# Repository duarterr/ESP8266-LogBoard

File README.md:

# ESP8266 LogBoard

A development platform for the ESP8266 with data logger capabilities. Fully compatible with the Arduino IDE.

Author: Renan R. Duarte - <duarte.renan@hotmail.com>

## Features
 - **ESP8266 (ESP12E) microcontroller:** The board is based on the ESP12E module, featuring the ESP8266 microcontroller. The module is configured in DIO SPI mode, so two extras GPIO pins can be used by the application (13 GPIOs in total).
 - **MicroSD card:** Data can be easily stored in a standard microSD card.
 - **Temperature sensor:** The Maxim DS1722 SPI temperature sensor can be used to measure the temperature.
 - **Real-time clock:** A Maxim DS1391 battery-backed SPI real-time clock provides timing capabilities without needing the internet.
 - **Onboard battery charger:** The board can be powered directly from the USB port or by a lithium battery. The onboard battery charger can be configured to fully charge the battery (4.2V) for cyclic use or float charge with a lower voltage (4.1V) to extend battery life in applications where the USB power is always connected.
 - **Switched-mode power supply:** A Maxim MAX8625 buck-boost controller IC provides a high efficiency continuous 3.3V bus to the system.
 - **Onboard programmer:** The device can be programmed directly by the USB port using the onboard USB-Serial bridge (FTDI FT232RQ). This device also enables serial communications between the microcontroller and a PC.

## Repository Contents

* **/Hardware** - PCB related files (EAGLE v9.5.5 and Sketchup 2018).
* **/Firmware** - Arduino example sketches to make use of it. 
* **/Extras** - Images and other stuff. 

## License Information

All contents of this repository are released under [Creative Commons Share-alike 4.0](http://creativecommons.org/licenses/by-sa/4.0/).

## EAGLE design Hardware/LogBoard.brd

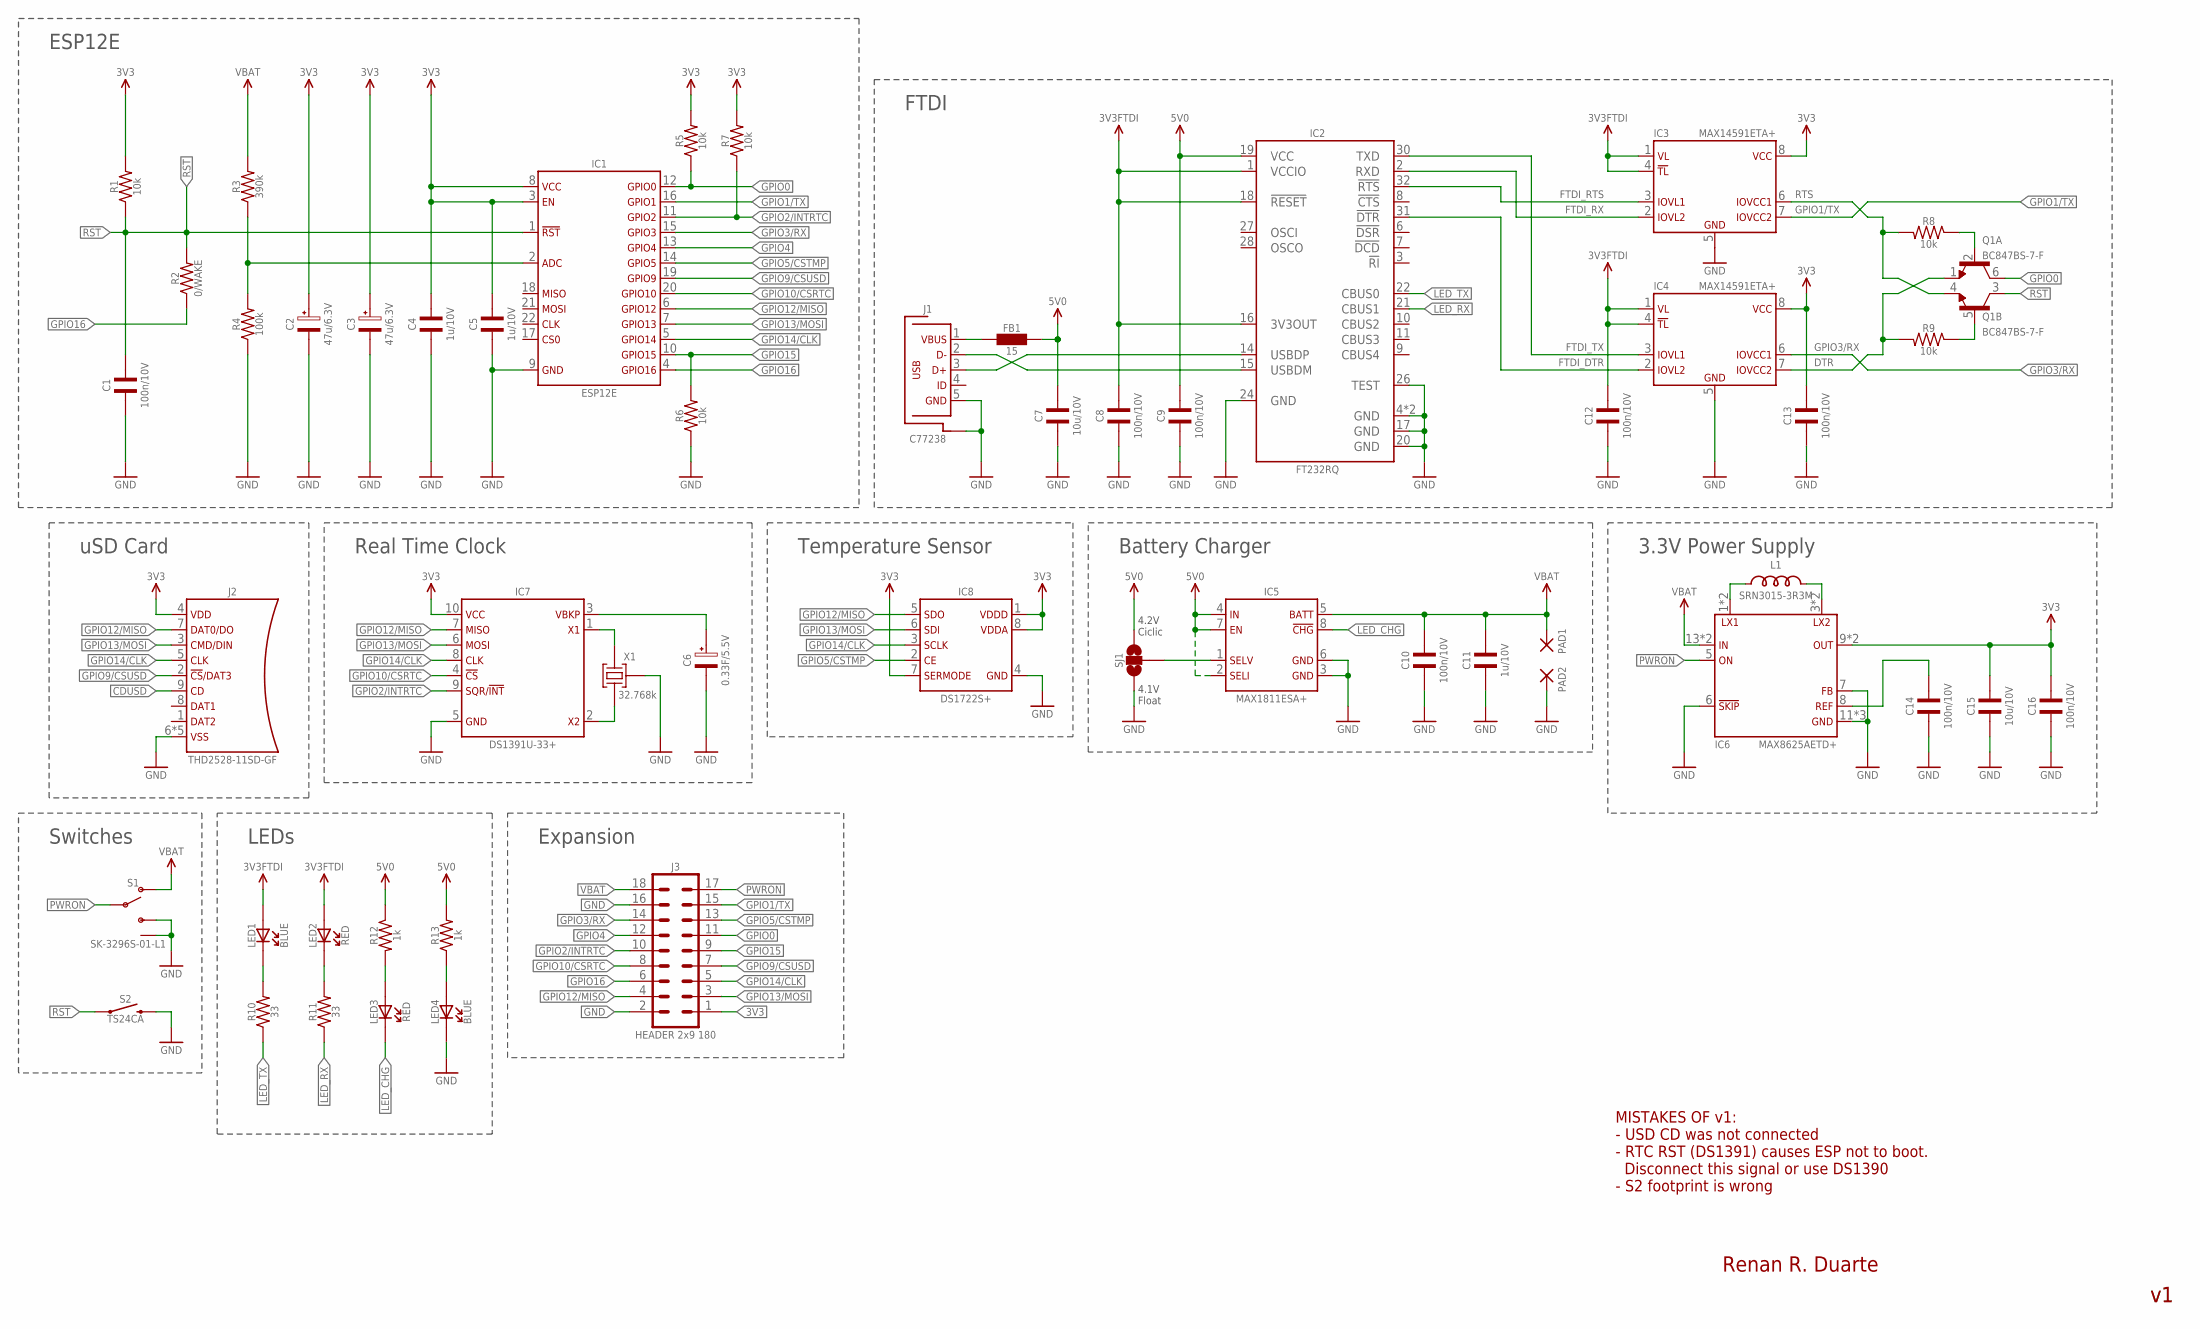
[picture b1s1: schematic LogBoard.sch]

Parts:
C1, C8, C9, C10, C12, C13, C14, C16: 100n/10V; C-SMD-0603
C2, C3: 47u/6.3V; C-SMD-CT3528
C4, C5, C11: 1u/10V; C-SMD-0603
C6: 0.33F/5.5V; C-PTH-5X11.5
C7, C15: 10u/10V; C-SMD-0603
FB1: 15; R-SMD-0603
IC1: ESP12E; IC-ESP8266-12E
IC2: FT232RQ; IC-QFN32
IC3, IC4: MAX14591ETA+; IC-TDFN8
IC5: MAX1811ESA+; IC-SO8
IC6: MAX8625AETD+; IC-TDFN14
IC7: DS1391U-33+; IC-USOP10
IC8: DS1722S+; IC-SO8
J1: C77238; CN-MICRO-USB
J2: THD2528-11SD-GF; CN-MICROSD
J3: HEADER 2x9 180; PH-9X2-180
L1: SRN3015-3R3M; L-SMD-3X3
LED1, LED4: BLUE; LED-SMD-0603
LED2, LED3: RED; LED-SMD-0603
PAD1, PAD2: SMD2; SMD1,27-2,54
Q1: BC847BS-7-F; IC-SOT363
R1, R5, R6, R7, R8, R9: 10k; R-SMD-0603
R2: 0/WAKE; R-SMD-0603
R3: 390k; R-SMD-0603
R4: 100k; R-SMD-0603
R10, R11: 33; R-SMD-0603
R12, R13: 1k; R-SMD-0603
S1: SK-3296S-01-L1; SWITCH_SPST_SMD_A
S2: TS24CA; TACTILE_SWITCH_SMD_RIGHT_ANGLE
SJ1: SJ-3
X1: 32.768k; CRYSTAL-SMD-7X1.5

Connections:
3V3: C2.+, C3.+, C4.P$1 (1), C5.P$1 (1), C13.P$2 (2), C15.P$1 (1), C16.P$1 (1), IC1.3 (EN), IC1.8 (VCC), IC3.8 (VCC), IC4.8 (VCC), IC6.9 (OUT), IC6.10 (OUT), IC7.10 (VCC), IC8.1 (VDDD), IC8.7 (SERMODE), IC8.8 (VDDA), J2.4 (VDD), J3.1, R1.P$2 (2), R5.P$2 (2), R7.P$2 (2)
3V3FTDI: C8.P$2 (2), C12.P$2 (2), IC2.1 (VCCIO), IC2.16 (3V3OUT), IC2.18 (!RESET), IC3.1 (VL), IC3.4 (!TL), IC4.1 (VL), IC4.4 (!TL), LED1.A, LED2.A
5V0: C7.P$2 (2), C9.P$2 (2), FB1.P$2 (2), IC2.19 (VCC), IC5.2 (SELI), IC5.4 (IN), IC5.7 (EN), R12.P$1 (1), R13.P$2 (2), SJ1.1
CDUSD: J2.9 (CD)
DTR: IC4.7 (IOVCC2), Q1.1 (E), R9.P$2 (2)
FTDI_DTR: IC2.31 (!DTR), IC4.2 (IOVL2)
FTDI_RTS: IC2.32 (!RTS), IC3.3 (IOVL1)
FTDI_RX: IC2.2 (RXD), IC3.2 (IOVL2)
FTDI_TX: IC2.30 (TXD), IC4.3 (IOVL1)
GND: C1.P$1 (1), C2.- (N), C3.- (N), C4.P$2 (2), C5.P$2 (2), C6.N, C7.P$1 (1), C8.P$1 (1), C9.P$1 (1), C10.P$2 (2), C11.P$2 (2), C12.P$1 (1), C13.P$1 (1), C14.P$2 (2), C15.P$2 (2), C16.P$2 (2), IC1.9 (GND), IC2.4 (GND), IC2.17 (GND), IC2.20 (GND), IC2.24 (GND), IC2.26 (TEST), IC2.GND, IC3.5 (GND), IC4.5 (GND), IC5.3 (GND), IC5.6 (GND), IC6.6 (!SKIP), IC6.7 (FB), IC6.11 (GND), IC6.12 (GND), IC6.TP (GND), IC7.5 (GND), IC8.4 (GND), J1.5 (GND), J1.SHELL (SHIELD), J1.SHELL1 (SHIELD), J1.SHELL2 (SHIELD), J1.SHELL3 (SHIELD), J2.6 (VSS), J2.G1 (VSS), J2.G2 (VSS), J2.G3 (VSS), J2.G4 (VSS), J3.2, J3.16, LED4.C, PAD2.1, R4.P$1 (1), R6.P$1 (1), S1.3 (S), S1.GND1, S1.GND2, S1.GND3, S1.GND4, S2.2, SJ1.3, X1.3 (2), X1.4 (2)
GPIO0: IC1.12 (GPIO0), J3.11, Q1.6 (C), R5.P$1 (1)
GPIO1/TX: IC1.16 (GPIO1), IC3.7 (IOVCC2), J3.15
GPIO2/INTRTC: IC1.11 (GPIO2), IC7.9 (INT), J3.10, R7.P$1 (1)
GPIO3/RX: IC1.15 (GPIO3), IC4.6 (IOVCC1), J3.14
GPIO4: IC1.13 (GPIO4), J3.12
GPIO5/CSTMP: IC1.14 (GPIO5), IC8.2 (CE), J3.13
GPIO9/CSUSD: IC1.19 (GPIO9), J2.2 (CD_DAT3_CS), J3.7
GPIO10/CSRTC: IC1.20 (GPIO10), IC7.4 (CS), J3.8
GPIO12/MISO: IC1.6 (GPIO12), IC7.7 (MISO), IC8.5 (SDO), J2.7 (DAT0_DO), J3.4
GPIO13/MOSI: IC1.7 (GPIO13), IC7.6 (MOSI), IC8.6 (SDI), J2.3 (CMD_DIN), J3.3
GPIO14/CLK: IC1.5 (GPIO14), IC7.8 (CLK), IC8.3 (SCLK), J2.5 (CLK), J3.5
GPIO15: IC1.10 (GPIO15), J3.9, R6.P$2 (2)
GPIO16: IC1.4 (GPIO16), J3.6, R2.P$1 (1)
LED_CHG: IC5.8 (!CHG), LED3.C
LED_RX: IC2.21 (CBUS1), R11.P$1 (1)
LED_TX: IC2.22 (CBUS0), R10.P$1 (1)
unnamed: Q1.2 (B), R8.P$1 (1)
unnamed: Q1.5 (B), R9.P$1 (1)
unnamed: FB1.P$1 (1), J1.1 (VBUS)
unnamed: IC2.15 (USBDM), J1.2 (D-)
unnamed: IC2.14 (USBDP), J1.3 (D+)
unnamed: LED1.C, R10.P$2 (2)
unnamed: LED2.C, R11.P$2 (2)
unnamed: LED3.A, R12.P$2 (2)
unnamed: IC5.1 (SELV), SJ1.2
unnamed: IC6.1 (LX1), IC6.2 (LX1), L1.P$1 (1)
unnamed: IC6.3 (LX2), IC6.4 (LX2), L1.P$2 (2)
unnamed: IC1.2 (ADC), R3.P$1 (1), R4.P$2 (2)
unnamed: IC7.1 (X1), X1.2 (3)
unnamed: IC7.2 (X2), X1.1
unnamed: C14.P$1 (1), IC6.8 (REF)
unnamed: LED4.A, R13.P$1 (1)
PWRON: IC6.5 (ON), J3.17, S1.2
RST: C1.P$2 (2), IC1.1 (RST), Q1.3 (C), R1.P$1 (1), R2.P$2 (2), S2.1
RTS: IC3.6 (IOVCC1), Q1.4 (E), R8.P$2 (2)
VBAT: C10.P$1 (1), C11.P$1 (1), IC5.5 (BATT), IC6.13 (IN), IC6.14 (IN), J3.18, PAD1.1, R3.P$2 (2), S1.1 (O)
VBKP: C6.P, IC7.3 (VBKP)

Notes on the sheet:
4.1V Float
4.2V Ciclic
FTDI
Battery Charger
3.3V Power Supply
ESP12E
Expansion
uSD Card
Real Time Clock
LEDs
Switches
Temperature Sensor
MISTAKES OF v1: - USD CD was not connected - RTC RST (DS1391) causes ESP not to boot. Disconnect this signal or use DS1390 - S2 footprint is wrong
Renan R. Duarte

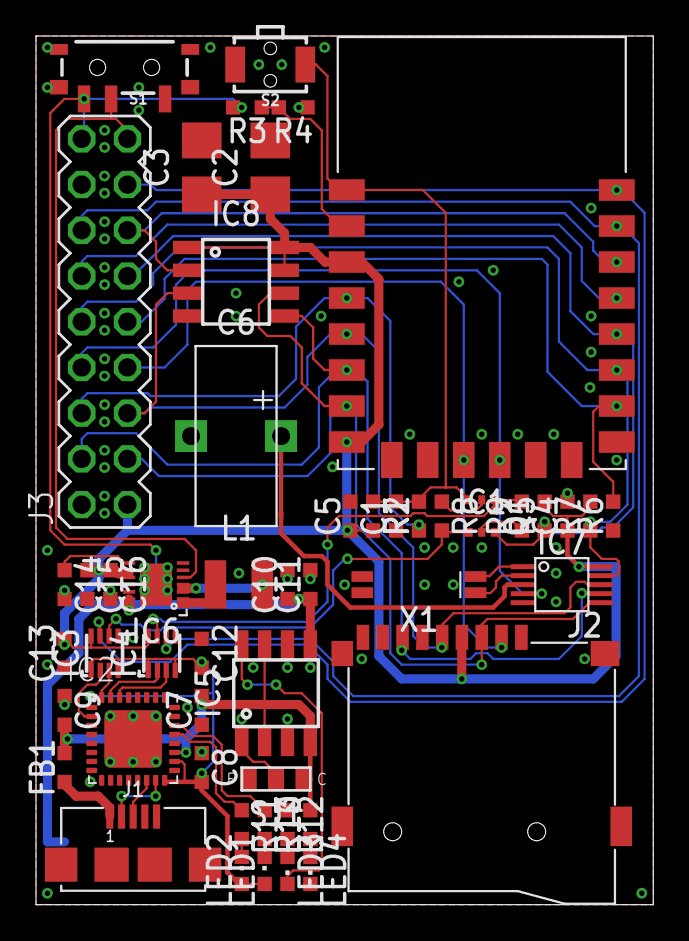
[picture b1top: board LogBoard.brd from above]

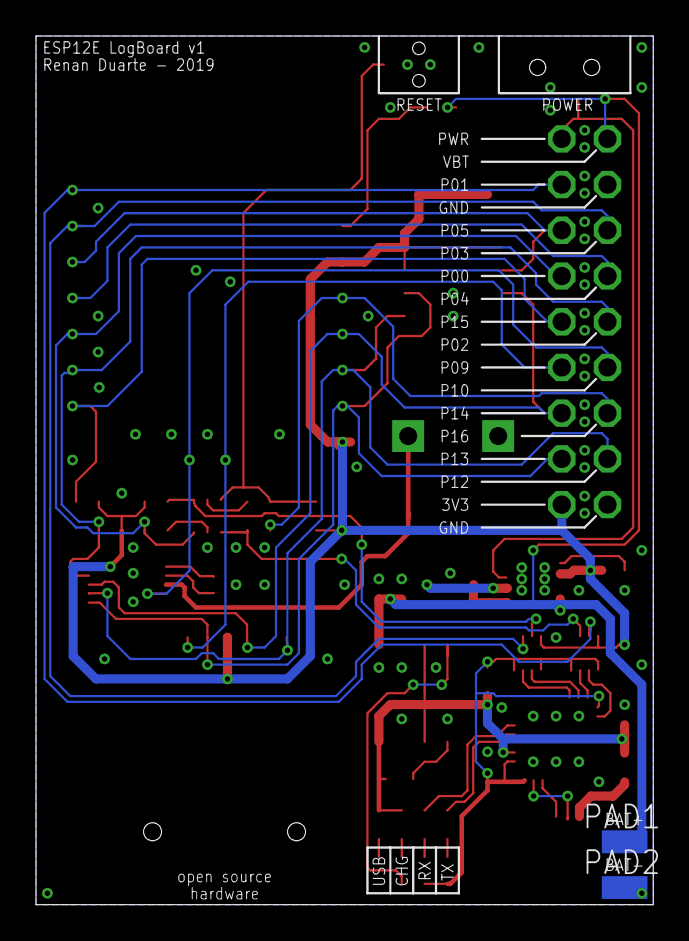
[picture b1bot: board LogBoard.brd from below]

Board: 2 copper layers, 34.3 x 48.3 mm, 54 parts (3 on the bottom side), 46 nets.

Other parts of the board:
U$7: OSHW_5MM

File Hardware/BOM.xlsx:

Part | Value | Description | Package
C1 | 100n/10V | 0603 SMD capacitor | 0603
C2 | 47u/6.3V | CT3528 SMD tantalum capacitor | CT3528
C3 | 47u/6.3V | CT3528 SMD tantalum capacitor | CT3528
C4 | 1u/10V | 0603 SMD capacitor | 0603
C5 | 1u/10V | 0603 SMD capacitor | 0603
C6 | 0.33F/5.5V - KR-5R5V334-R | Coin cell supercapacitor | PTH 5X11.5
C7 | 10u/10V | 0603 SMD capacitor | 0603
C8 | 100n/10V | 0603 SMD capacitor | 0603
C9 | 100n/10V | 0603 SMD capacitor | 0603
C10 | 100n/10V | 0603 SMD capacitor | 0603
C11 | 1u/10V | 0603 SMD capacitor | 0603
C12 | 100n/10V | 0603 SMD capacitor | 0603
C13 | 100n/10V | 0603 SMD capacitor | 0603
C14 | 100n/10V | 0603 SMD capacitor | 0603
C15 | 10u/10V | 0603 SMD capacitor | 0603
C16 | 100n/10V | 0603 SMD capacitor | 0603
FB1 | 15 | 0603 SMD ferrite bead | 0603
IC1 | ESP12E | ESP12E module | IC-ESP8266-12E
IC2 | FT232RQ | USB UART IC | QFN32
IC3 | MAX14591ETA+ | Logic level translator | TDFN8
IC4 | MAX14591ETA+ | Logic level translator | TDFN8
IC5 | MAX1811ESA+ | USB-Powered Li+ Charger | SO8
IC6 | MAX8625AETD+ | Step-Up/Down DC-DC Converter | TDFN14
IC7 | DS1391U-33+ | Low-Voltage SPI/3-Wire RTCs with Trickle Charger | USOP10
IC8 | DS1722S+ | Digital Thermometer with SPI/3-Wire Interface | SO8
J1 | C77238 | Micro USB 5P B SMD | Micro USB 5P B SMD
J2 | THD2528-11SD-GF | Micro SD card SMD connector | Micro SD card SMD connector
J3 | HEADER 2x9 180 | 09x2 0.1" pitch male header | 09x2 0.1" pitch male header
L1 | SRN3015-3R3M | 3x3mm SMD inductor | 3x3mm SMD inductor
LED1 | BLUE | 0603 SMD LED | 0603
LED2 | RED | 0603 SMD LED | 0603
LED3 | RED | 0603 SMD LED | 0603
LED4 | BLUE | 0603 SMD LED | 0603
Q1 | BC847BS-7-F | Dual NPN transistor | SOT363
R1 | 10k | 0603 SMD resistor | 0603
R2 | 0/WAKE | 0603 SMD resistor | 0603
R3 | 390k | 0603 SMD resistor | 0603
R4 | 100k | 0603 SMD resistor | 0603
R5 | 10k | 0603 SMD resistor | 0603
R6 | 10k | 0603 SMD resistor | 0603
R7 | 10k | 0603 SMD resistor | 0603
R8 | 10k | 0603 SMD resistor | 0603
R9 | 10k | 0603 SMD resistor | 0603
R10 | 33 | 0603 SMD resistor | 0603
R11 | 33 | 0603 SMD resistor | 0603
R12 | 1k | 0603 SMD resistor | 0603
R13 | 1k | 0603 SMD resistor | 0603
S1 | SK-3296S-01-L1 | Right angle SMD slide switch | Right angle SMD slide switch
S2 | TS24CA | Right angle SMD momentary switch | Right angle SMD momentary switch
X1 | SSP-T7-F 32.768kHz 20PPM7pF | 7015 SMD crystal oscillator | 7015 4P

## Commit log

2019-10-15 Updated Eagle PCB
2019-10-15 Updated BOM
2019-10-15 Added PDF schematic
2019-10-15 Added info regarding SPI DIO mode
2019-10-16 WiFi log via HTTPs
2019-10-16 WiFi log working
2019-10-16 WiFi log possible without SD card
2019-10-16 Added EEPROM functions
2019-10-16 Added EEPROMWrite example
2019-10-17 Load config from SD card
2019-10-17 Added firmware update via SD card
2019-10-17 Added Google Script code
2019-10-17 Updated EEPROMWrite example
2019-10-17 Reorganized folder structure
2019-10-17 Added NTP time update
2019-10-17 Unreachable states corrected
2019-10-18 Firmware v1.0
2019-10-19 v1.1 Not finished yet
2019-10-20 Post working. Missing SD card log
2019-10-20 Backup before changing CONFIG to SETTINGS
2019-10-20 Changed CONFIG to SETTINGS
2019-10-20 v1.1 - Everything working. Sync not implemented yet
2019-10-21 Sync 99%. Missing replace line feature.
2019-10-21 v1.1 done. Missing only LineReplace feature of Sync
2019-10-21 Updated flowchart
2019-10-21 Flowchart rebuilt
2019-10-21 v1.1 Finished
2019-10-23 Test with new HTTP redirect php
2019-10-23 New HTTP redirect script working
2020-02-18 Added BME280 support
2020-05-19 Timeout increased (go horse)
2020-05-20 Added MAC to payload

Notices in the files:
parts and their libraries:
SparkFun-Switches: Licensing: Creative Commons ShareAlike 4.0 International - https://creativecommons.org/licenses/by-sa/4.0
